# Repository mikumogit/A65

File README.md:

# Malic Acid A65
**Malic Acid A65** is 65% ALPS switches Keyboard designed for GL516 case & AEK keycaps.

**Layouts**

**Designed for GL516**

The GL516 case is required to use Malic Acid A65.<br>
You can buy the GL516 case [YushaKobo](https://shop.yushakobo.jp/collections/case/products/3814) .<br>
Or you can fabricate your own from [publicly available 3D data](https://github.com/Salicylic-acid3/GL516_Case).

**Version History**

- Rev 0.1…  Prototype edition.

- Rev 1.0…  Added stabilizer holes to allow the Right Option key to be installed in the upward position. / Fixed reset switch position.   

***
GL516 Template is Released under the MIT license.<br>
Copyright 2020 Salicylic_acid3<br>
[https://github.com/Salicylic-acid3/GL516_Template/blob/main/Licence.txt](https://github.com/Salicylic-acid3/GL516_Template/blob/main/Licence.txt)

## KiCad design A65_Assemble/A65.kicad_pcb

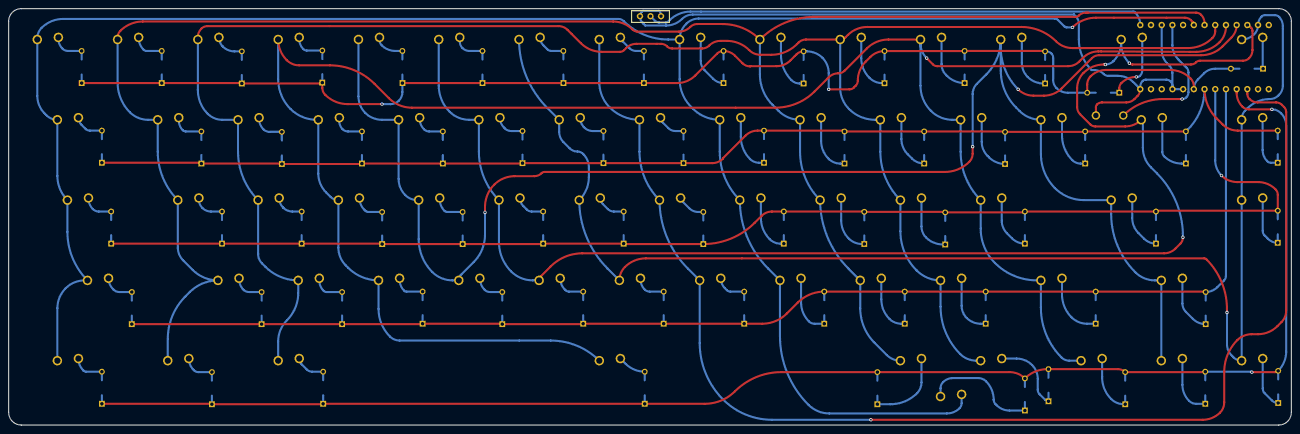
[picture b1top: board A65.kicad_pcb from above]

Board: 2 copper layers, 304.4 x 98.8 mm, 137 parts (0 on the bottom side), 83 nets.

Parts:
D1, D2, D3, D4, D5, D6, D7, D8, D9, D10, D11, D12, D13, D14, D15, D16, D17, D18, D19, D20, D21, D22, D23, D24, D25, D26, D27, D28, D29, D30, D31, D32, D33, D34, D35, D36, D37, D38, D39, D40, D41, D42, D43, D44, D45, D46, D47, D48, D49, D50, D51, D52, D53, D54, D55, D56, D57, D58, D59, D60, D61, D62, D63, D64, D65, D66, D67: D; Diode_TH_SMD
J1: Conn_01x02; Battery_XH2.5_GL_PCB
SW1, SW6, SW7, SW8, SW9, SW11, SW12, SW13, SW14, SW16, SW17, SW18, SW19, SW21, SW22, SW23, SW24, SW25, SW26, SW27, SW28, SW29, SW30, SW31, SW32, SW33, SW34, SW35, SW36, SW37, SW38, SW39, SW40, SW42, SW43, SW44, SW45, SW46, SW47, SW48, SW49, SW50, SW51, SW52, SW53, SW54, SW56, SW57, SW58, SW60, SW61, SW64, SW65, SW66, SW67: SW_PUSH; ALPS-1U
SW2, SW5, SW15, SW55, SW63: SW_PUSH; ALPS-1.5U
SW3: SW_PUSH; ALPS-1.75U
SW4, SW59: SW_PUSH; ALPS-2.25U
SW10: SW_PUSH; ALPS-1.25U
SW20: SW_PUSH; ALPS-6.5U
SW41, SW62: SW_PUSH; ALPS-2U
SW68: SW_PUSH; ResetSW
U1: BLEMicroPro; Micon_BMP_GL

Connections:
Bat+: J1.1, U1.25 (BAT+)
Col0: SW1.1, SW2.1, SW3.1, SW4.1, SW5.1, SW37.1, SW38.1, SW39.1, SW40.1, SW41.1, U1.20 (F4/PIN20)
Col1: SW6.1, SW7.1, SW8.1, SW9.1, SW10.1, SW42.1, SW43.1, SW44.1, SW45.1, SW46.1, U1.19 (F5/PIN19)
Col2: SW11.1, SW12.1, SW13.1, SW14.1, SW15.1, SW47.1, SW48.1, SW49.1, SW50.1, SW51.1, U1.18 (F6/PIN18)
Col3: SW16.1, SW17.1, SW18.1, SW19.1, SW20.1, SW52.1, SW53.1, SW54.1, SW55.1, SW56.1, U1.17 (F7/PIN17)
Col4: SW21.1, SW22.1, SW23.1, SW24.1, SW57.1, SW58.1, SW59.1, SW60.1, SW61.1, U1.16 (B1/PIN16)
Col5: SW25.1, SW26.1, SW27.1, SW28.1, SW62.1, SW63.1, U1.15 (B3/PIN15)
Col6: SW29.1, SW30.1, SW31.1, SW32.1, SW64.1, SW65.1, SW66.1, SW67.1, U1.14 (B2/PIN14)
Col7: SW33.1, SW34.1, SW35.1, SW36.1, U1.10 (E6/PIN10)
GND: J1.2, SW68.2, U1.3 (GND), U1.4 (GND), U1.23 (GND), U1.26 (BAT-)
unnamed: D1.2 (A), SW1.2
unnamed: D2.2 (A), SW2.2
unnamed: D3.2 (A), SW3.2
unnamed: D4.2 (A), SW4.2
unnamed: D5.2 (A), SW5.2
unnamed: D6.2 (A), SW6.2
unnamed: D7.2 (A), SW7.2
unnamed: D8.2 (A), SW8.2
unnamed: D9.2 (A), SW9.2
unnamed: D10.2 (A), SW10.2
unnamed: D11.2 (A), SW11.2
unnamed: D12.2 (A), SW12.2
unnamed: D13.2 (A), SW13.2
unnamed: D14.2 (A), SW14.2
unnamed: D15.2 (A), SW15.2
unnamed: D16.2 (A), SW16.2
unnamed: D17.2 (A), SW17.2
unnamed: D18.2 (A), SW18.2
unnamed: D19.2 (A), SW19.2
unnamed: D20.2 (A), SW20.2
unnamed: D21.2 (A), SW21.2
unnamed: D22.2 (A), SW22.2
unnamed: D23.2 (A), SW23.2
unnamed: D24.2 (A), SW24.2
unnamed: D25.2 (A), SW25.2
unnamed: D26.2 (A), SW26.2
unnamed: D27.2 (A), SW27.2
unnamed: D28.2 (A), SW28.2
unnamed: D29.2 (A), SW29.2
unnamed: D30.2 (A), SW30.2
unnamed: D31.2 (A), SW31.2
unnamed: D32.2 (A), SW32.2
unnamed: D33.2 (A), SW33.2
unnamed: D34.2 (A), SW34.2
unnamed: D35.2 (A), SW35.2
unnamed: D36.2 (A), SW36.2
unnamed: D37.1 (K), SW37.2
unnamed: D38.1 (K), SW38.2
unnamed: D39.1 (K), SW39.2
unnamed: D40.1 (K), SW40.2
unnamed: D41.1 (K), SW41.2
unnamed: D42.1 (K), SW42.2
unnamed: D43.1 (K), SW43.2
unnamed: D44.1 (K), SW44.2
unnamed: D45.1 (K), SW45.2
unnamed: D46.1 (K), SW46.2
unnamed: D47.1 (K), SW47.2
unnamed: D48.1 (K), SW48.2
unnamed: D49.1 (K), SW49.2
unnamed: D50.1 (K), SW50.2
unnamed: D51.1 (K), SW51.2
unnamed: D52.1 (K), SW52.2
unnamed: D53.1 (K), SW53.2
unnamed: D54.1 (K), SW54.2
unnamed: D55.1 (K), SW55.2
unnamed: D56.1 (K), SW56.2
unnamed: D57.1 (K), SW57.2
unnamed: D58.1 (K), SW58.2
unnamed: D59.1 (K), SW59.2
unnamed: D60.1 (K), SW60.2
unnamed: D61.1 (K), SW61.2
unnamed: D62.1 (K), SW62.2
unnamed: D63.1 (K), SW63.2
unnamed: D64.1 (K), SW64.2
unnamed: D65.1 (K), SW65.2
unnamed: D66.1 (K), SW66.2
unnamed: D67.1 (K), SW67.2
Reset: SW68.1, U1.22 (RST)
Row0: D1.1 (K), D6.1 (K), D11.1 (K), D16.1 (K), D21.1 (K), D25.1 (K), D29.1 (K), D33.1 (K), D37.2 (A), D42.2 (A), D47.2 (A), D52.2 (A), D57.2 (A), D62.2 (A), D64.2 (A), U1.5 (D1/PIN5/SDA)
Row1: D2.1 (K), D7.1 (K), D12.1 (K), D17.1 (K), D22.1 (K), D26.1 (K), D30.1 (K), D34.1 (K), D38.2 (A), D43.2 (A), D48.2 (A), D53.2 (A), D58.2 (A), D63.2 (A), D65.2 (A), U1.6 (D0/PIN6/SCL)
Row2: D3.1 (K), D8.1 (K), D13.1 (K), D18.1 (K), D23.1 (K), D27.1 (K), D31.1 (K), D35.1 (K), D39.2 (A), D44.2 (A), D49.2 (A), D54.2 (A), D59.2 (A), D66.2 (A), U1.7 (D4/PIN7)
Row3: D4.1 (K), D9.1 (K), D14.1 (K), D19.1 (K), D24.1 (K), D28.1 (K), D32.1 (K), D36.1 (K), D40.2 (A), D45.2 (A), D50.2 (A), D55.2 (A), D60.2 (A), U1.8 (C6/PIN8)
Row4: D5.1 (K), D10.1 (K), D15.1 (K), D20.1 (K), D41.2 (A), D46.2 (A), D51.2 (A), D56.2 (A), D61.2 (A), D67.2 (A), U1.9 (D7/PIN9)

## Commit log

2022-08-07 Add Files.
2022-08-07 Add license files.
2022-08-07 revise license text
2022-08-07 Add license text file for GL516 template.
2022-09-01 Fixed reset switch position.
